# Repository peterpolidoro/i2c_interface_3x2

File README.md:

# i2c_interface_3x2

Authors:

    Peter Polidoro <polidorop@janelia.hhmi.org>

License:

    BSD

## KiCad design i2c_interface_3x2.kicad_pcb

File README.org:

#+TITLE: i2c_interface_3x2
#+AUTHOR: Peter Polidoro
#+EMAIL: peter@polidoro.io

* Repository Information
  - Author :: Peter Polidoro
  - License :: Open-Source Hardware

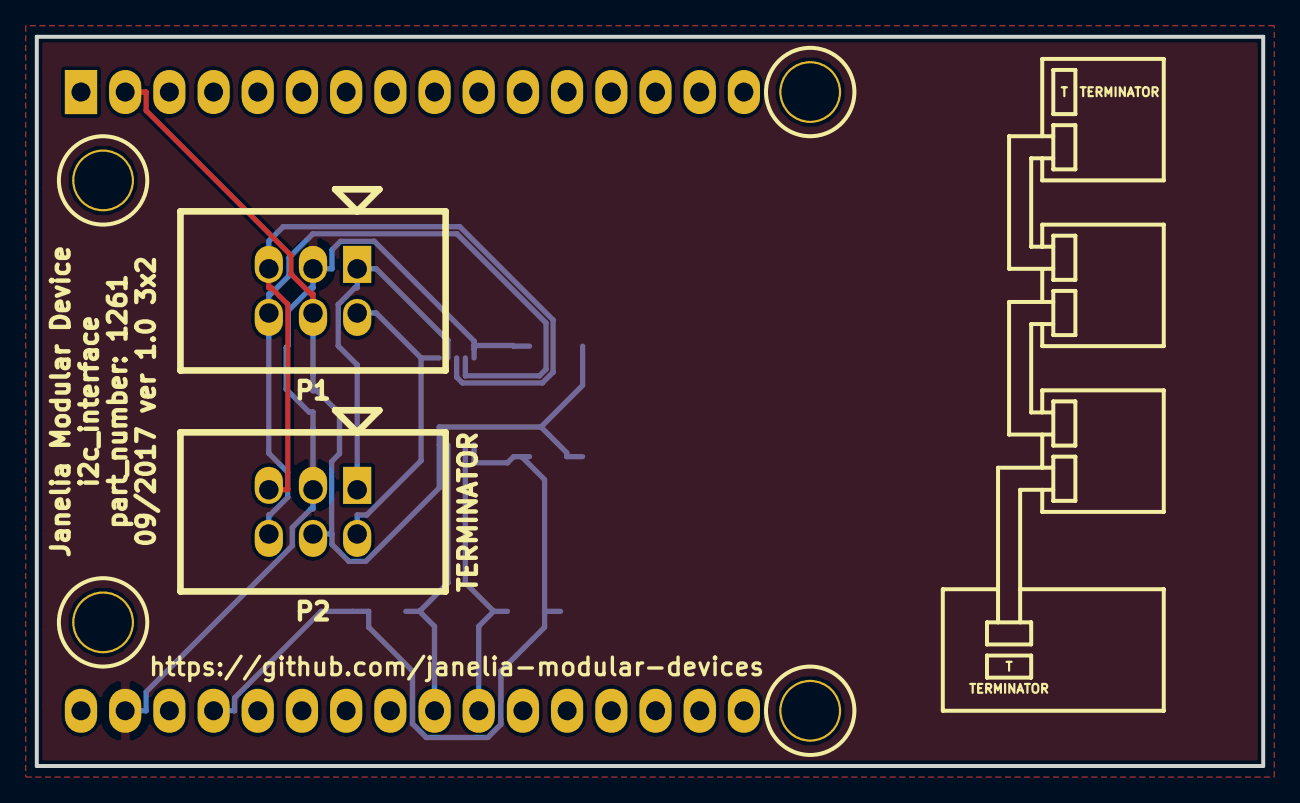
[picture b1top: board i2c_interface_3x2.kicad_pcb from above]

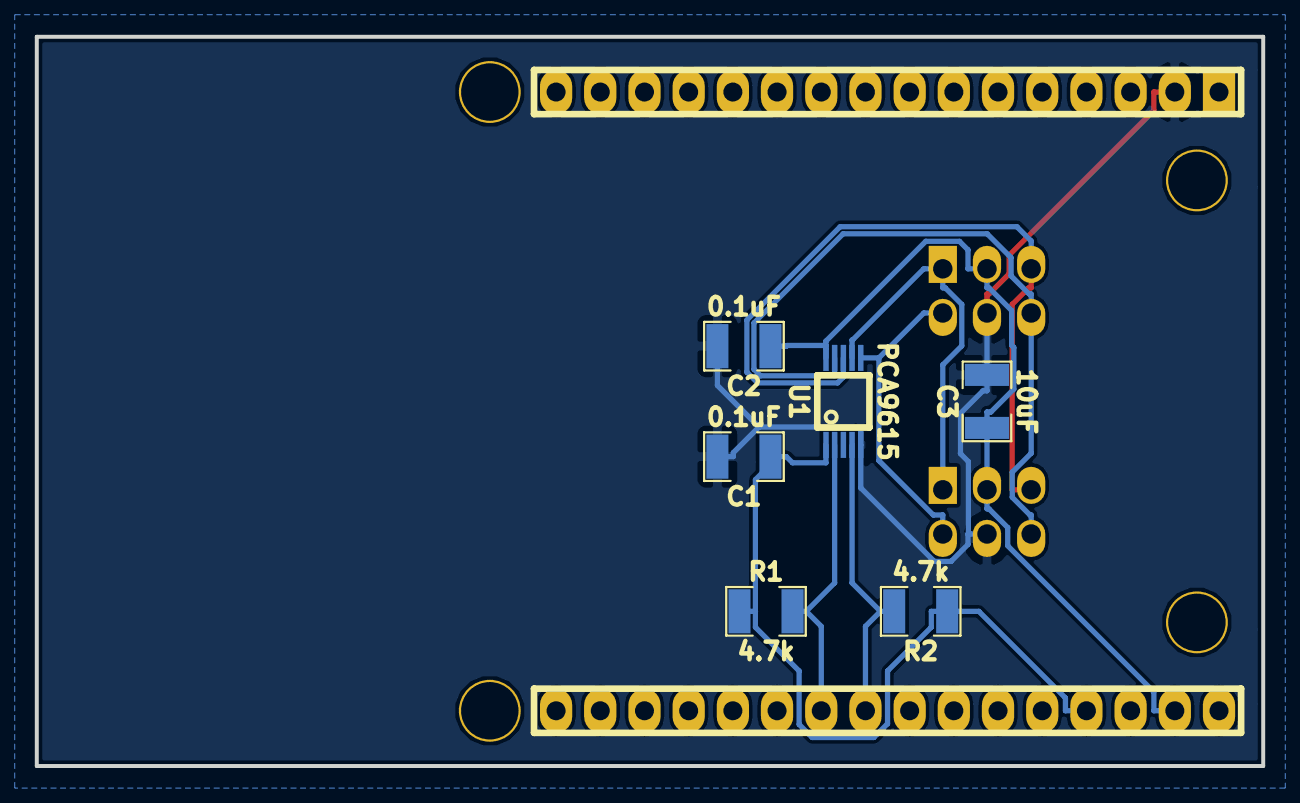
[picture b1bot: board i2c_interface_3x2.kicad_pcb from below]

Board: 2 copper layers, 70.5 x 41.9 mm, 9 parts (6 on the bottom side), 9 nets.

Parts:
C1, C2: 0.1uF; SM1210
C3: 10uF; SM1210
MDB1: MODULAR_DEVICE_BASE_3X2_MALE
P1, P2: HEADER_02X03; HEADER_02x03
R1, R2: 4.7k; SM1210
U1: PCA9615; TSSOP10

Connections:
+3V3: C1.1, MDB1.3V3, R1.1, R2.1, U1.1
/DSCLM: P1.2, P2.2, U1.6
/DSCLP: P1.1, P2.1, U1.7
/DSDAM: P1.6, P2.6, U1.9
/DSDAP: P1.5, P2.5, U1.8
/SCL: MDB1.19, R2.2, U1.4
/SDA: MDB1.18, R1.2, U1.2
GND: C1.2, C2.2, C3.2, MDB1.GND, P1.4, P2.4, U1.5
VEE: C2.1, C3.1, MDB1.VEE, P1.3, P2.3, U1.10

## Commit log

2017-09-19 Initial commit.
2017-09-19 Added footprints.
2017-09-21 Progress towards v1.0.
2017-09-22 Modifications.
2017-09-22 Removed extra libraries.
2017-09-22 Finished v1.0.
2017-09-22 Updated bom.
2018-01-08 Updated to v4.
2018-01-08 Added v4 files.
2018-01-08 Updated gitignore.
2018-03-09 Update license from software to hardware.
2018-04-12 README.md -> README.org.
2018-04-19 Added .DS_Store to .gitignore.
2018-05-16 Added generate_kicad_documentation submodule.
2018-05-17 Updated submodules.
2018-08-12 Marked extra Teensy pins.
2018-08-12 Removed v4 files.
2018-08-24 Removed F.SilkS from pads.
2021-09-16 Update email address
2021-09-21 Remove ignored files
2022-02-22 Add guix files
2022-02-23 Add guix documentation
2024-05-31 Add board image
